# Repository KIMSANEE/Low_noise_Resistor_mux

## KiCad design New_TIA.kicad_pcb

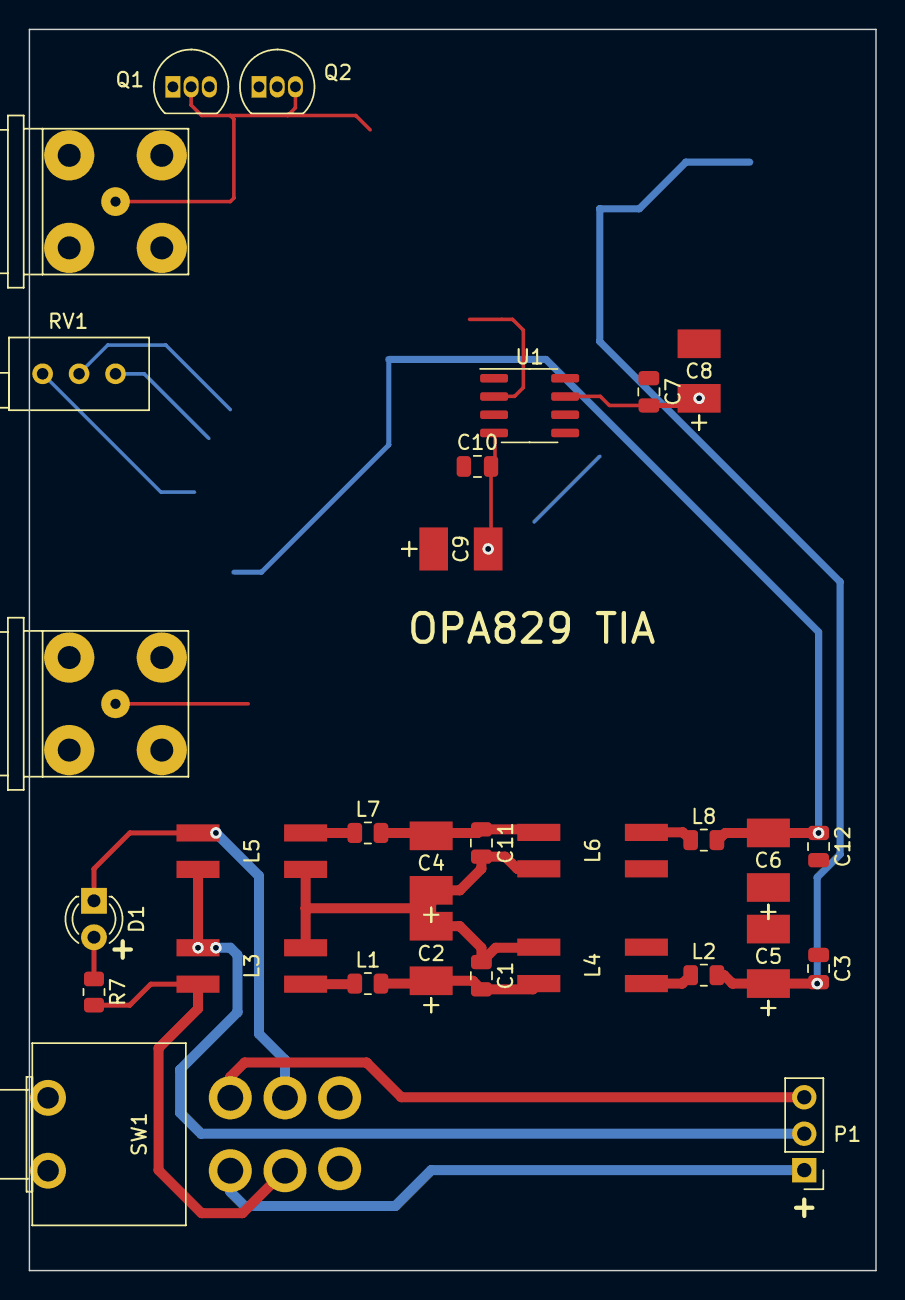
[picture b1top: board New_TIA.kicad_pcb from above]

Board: 2 copper layers, 59.0 x 86.5 mm, 30 parts (0 on the bottom side), 17 nets.

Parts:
C1, C3, C11, C12: 100nF; C_0805_2012Metric
C2, C4, C5, C6, C8, C9: 10uF; C_1210_POL_Mine
C7, C10: 0.1uF; C_0805_2012Metric
D1: LED; LED_D3.0mm
L1, L2, L7, L8: FB 600 Ohm; R_0805_2012Metric
L3, L4, L5, L6: L_Core_Ferrite_Coupled_1423; Murata_Choke_1423
P1: CONN_01X03; PinHeader_1x03_P2.54mm_Vertical
P2, P3: BNC; BNC_PCB_90degree
Q1, Q2: 2N3904; TO-92_Inline
R7: 2.2k; R_0805_2012Metric
RV1: 10K; Potentiometer_Bourns_3296X_Horizontal
SW1: Toggle_SW_PCB; Toggle_PCB
U1: OPA828; SOIC-8_3.9x4.9mm_P1.27mm

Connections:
+12VA: C3.2, C5.1, C7.2, C8.1, L2.2
-12VA: C6.2, C9.2, C10.2, C12.1, L8.2
GNDA: C3.1, C5.2, C6.1, C7.1, C8.2, C9.1, C10.1, C12.2, L4.4, L6.3, P2.2, P3.2, Q1.3, Q2.2
unnamed: C1.1, C2.2, C4.1, C11.2, L3.4, L4.1, L5.3, L6.2
unnamed: C1.2, C2.1, L1.2, L4.2
unnamed: C4.2, C11.1, L6.1, L7.2
unnamed: P2.1, Q1.2, Q2.3
unnamed: D1.1, L5.1, SW1.2
unnamed: D1.2, R7.1
unnamed: L1.1, L3.3
unnamed: L2.1, L4.3
unnamed: L3.1, L5.2, P1.2
unnamed: L3.2, R7.2, SW1.5
unnamed: L5.4, L7.1
unnamed: L6.4, L8.1
unnamed: P1.1, SW1.4
unnamed: P1.3, SW1.1

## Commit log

2024-04-24 new file: Front Panel.ipt new file: LIB_TIA.bak new file: LIB_TIA.bck new file: LIB_TIA.dcm new file: LIB_TIA.lib new file: Library.pretty/CAS-D20A1.kicad_mod new file: MYParts.pretty/2N4117.kicad_mo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
